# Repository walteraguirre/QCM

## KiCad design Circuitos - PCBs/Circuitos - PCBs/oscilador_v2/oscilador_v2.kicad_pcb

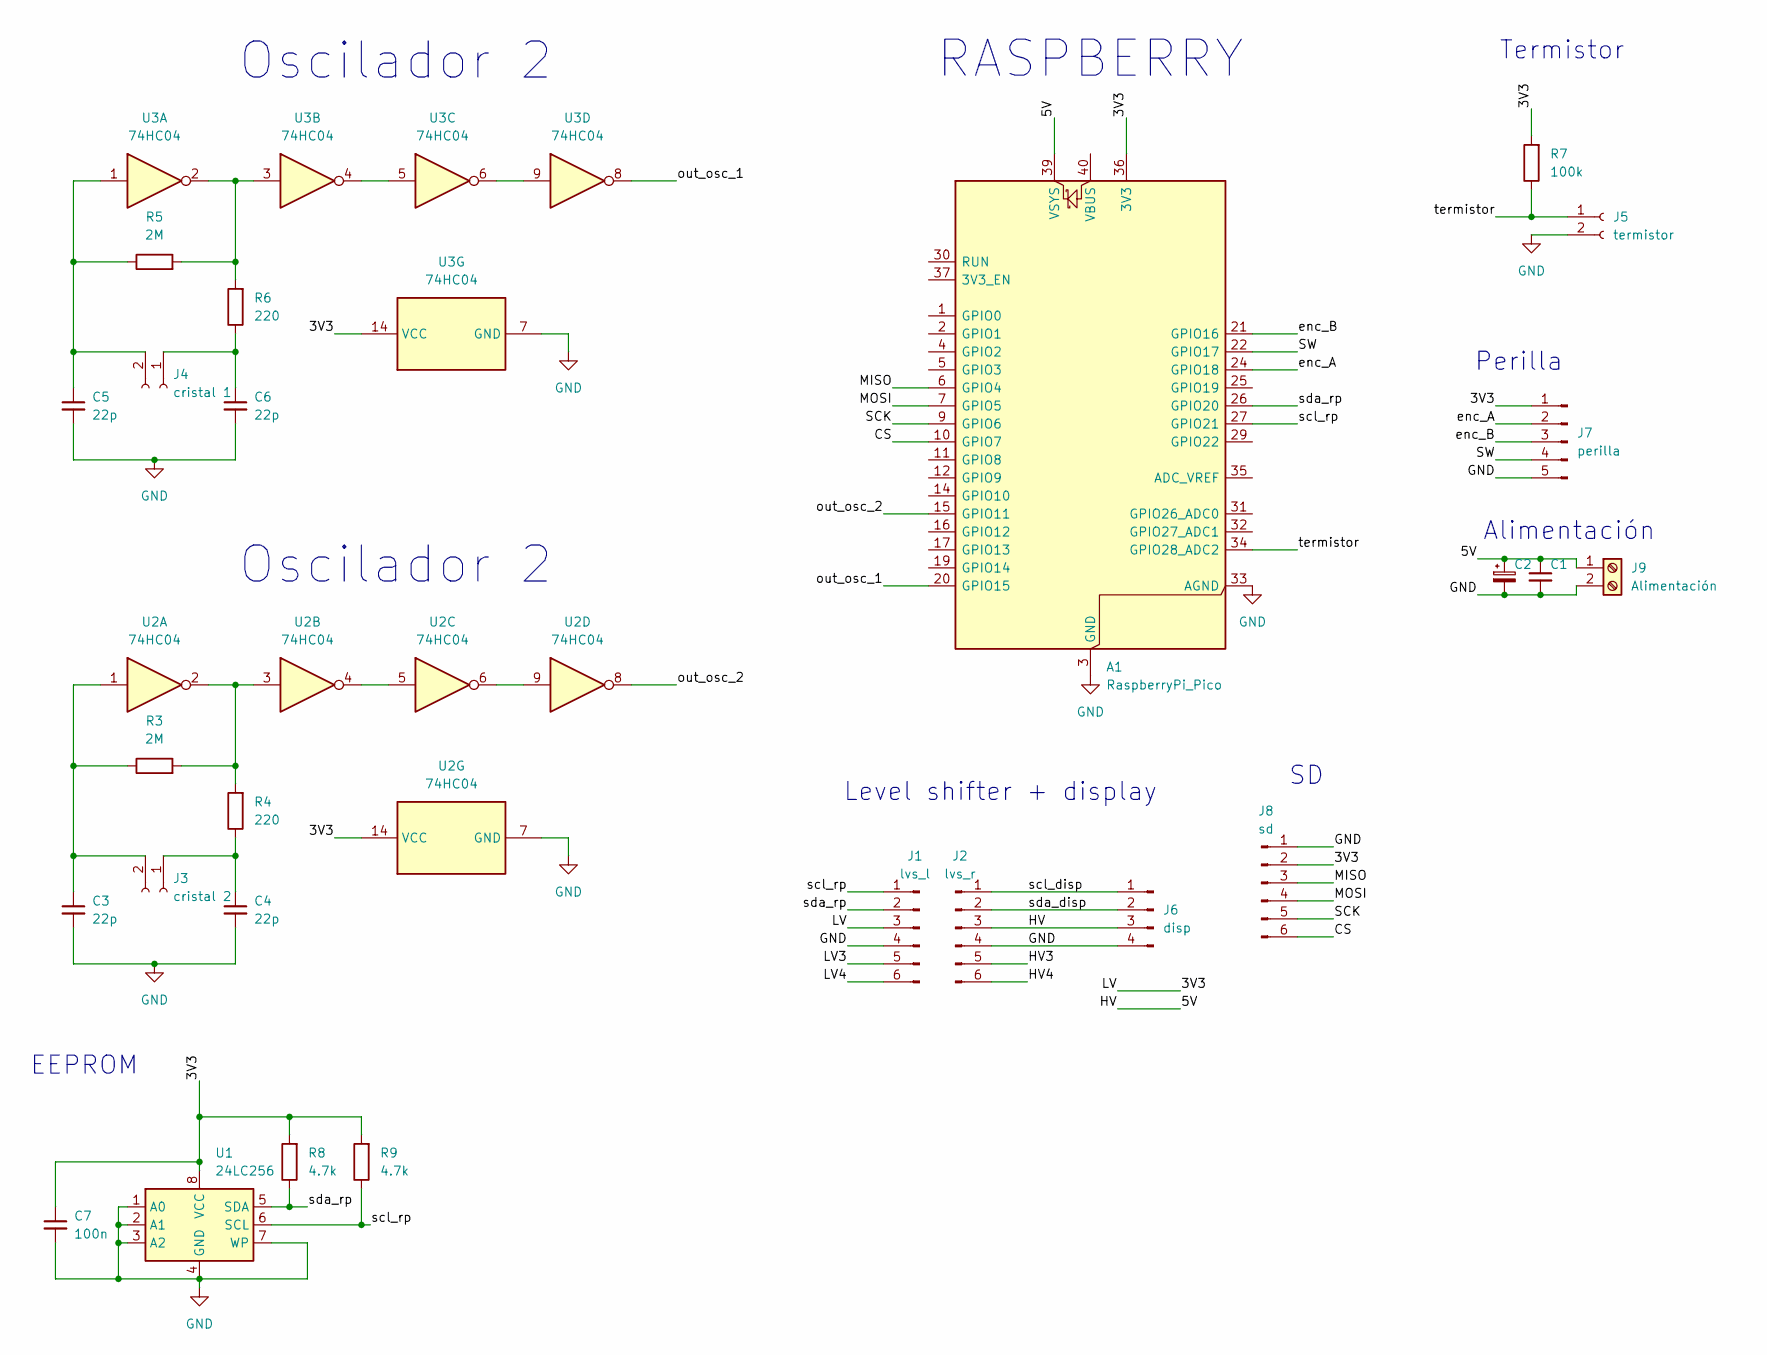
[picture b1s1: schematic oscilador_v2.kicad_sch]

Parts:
A1: RaspberryPi_Pico; RaspberryPi_Pico_Common_Unspecified
C1: C_Small; C_Disc_D10.0mm_W2.5mm_P5.00mm
C2: C_Polarized_Small; CP_Radial_D5.0mm_P2.50mm
C3, C4, C5, C6: 22p; C_Disc_D10.0mm_W2.5mm_P5.00mm
C7: 100n; C_Disc_D10.0mm_W2.5mm_P5.00mm
J1: lvs_l; PinSocket_1x06_P2.54mm_Vertical
J2: lvs_r; PinSocket_1x06_P2.54mm_Vertical
J3: cristal 2; JST_EH_B2B-EH-A_1x02_P2.50mm_Vertical
J4: cristal 1; JST_EH_B2B-EH-A_1x02_P2.50mm_Vertical
J5: termistor; JST_EH_B2B-EH-A_1x02_P2.50mm_Vertical
J6: disp; PinHeader_1x04_P2.54mm_Vertical
J7: perilla; PinHeader_1x05_P2.54mm_Vertical
J8: sd; PinSocket_1x06_P2.54mm_Vertical
J9: Alimentación; TerminalBlock_MaiXu_MX126-5.0-02P_1x02_P5.00mm
R3, R5: 2M; R_Axial_DIN0207_L6.3mm_D2.5mm_P10.16mm_Horizontal
R4, R6: 220; R_Axial_DIN0207_L6.3mm_D2.5mm_P10.16mm_Horizontal
R7: 100k; R_Axial_DIN0207_L6.3mm_D2.5mm_P10.16mm_Horizontal
R8, R9: 4.7k; R_Axial_DIN0207_L6.3mm_D2.5mm_P10.16mm_Horizontal
U1: 24LC256; DIP-8_W7.62mm_LongPads
U2, U3: 74HC04; DIP-14_W7.62mm

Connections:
/3V3: A1.36 (3V3), C7.1, J1.3, J7.1, J8.2, R7.2, R8.2, R9.2, U1.8 (VCC), U2.14 (VCC), U3.14 (VCC)
/5V: A1.39 (VSYS), C1.1, C2.1, J2.3, J6.3, J9.1
/CS: A1.10 (GPIO7), J8.6
/HV3: J2.5
/HV4: J2.6
/LV3: J1.5
/LV4: J1.6
/MISO: A1.6 (GPIO4), J8.3
/MOSI: A1.7 (GPIO5), J8.4
/SCK: A1.9 (GPIO6), J8.5
/SW: A1.22 (GPIO17), J7.4
/enc_A: A1.24 (GPIO18), J7.2
/enc_B: A1.21 (GPIO16), J7.3
/out_osc_1: A1.20 (GPIO15), U3.8
/out_osc_2: A1.15 (GPIO11), U2.8
/scl_disp: J2.1, J6.1
/scl_rp: A1.27 (GPIO21), J1.1, R9.1, U1.6 (SCL)
/sda_disp: J2.2, J6.2
/sda_rp: A1.26 (GPIO20), J1.2, R8.1, U1.5 (SDA)
/termistor: A1.34 (GPIO28_ADC2), J5.1, R7.1
GND: A1.3 (GND), A1.8 (GND), A1.13 (GND), A1.18 (GND), A1.23 (GND), A1.28 (GND), A1.33 (AGND), A1.38 (GND), C1.2, C2.2, C3.2, C4.2, C5.2, C6.2, C7.2, J1.4, J2.4, J5.2, J6.4, J7.5, J8.1, J9.2, U1.1 (A0), U1.2 (A1), U1.3 (A2), U1.4 (GND), U1.7 (WP), U2.7 (GND), U3.7 (GND)
unnamed: C4.1, J3.1, R4.1
unnamed: C3.1, J3.2, R3.1, U2.1
unnamed: C6.1, J4.1, R6.1
unnamed: C5.1, J4.2, R5.1, U3.1
unnamed: R3.2, R4.2, U2.2, U2.3
unnamed: R5.2, R6.2, U3.2, U3.3
unnamed: U2.4, U2.5
unnamed: U2.6, U2.9
unnamed: U3.4, U3.5
unnamed: U3.6, U3.9

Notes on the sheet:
Level shifter + display
Perilla
Alimentación
Oscilador 2
EEPROM
Termistor
RASPBERRY

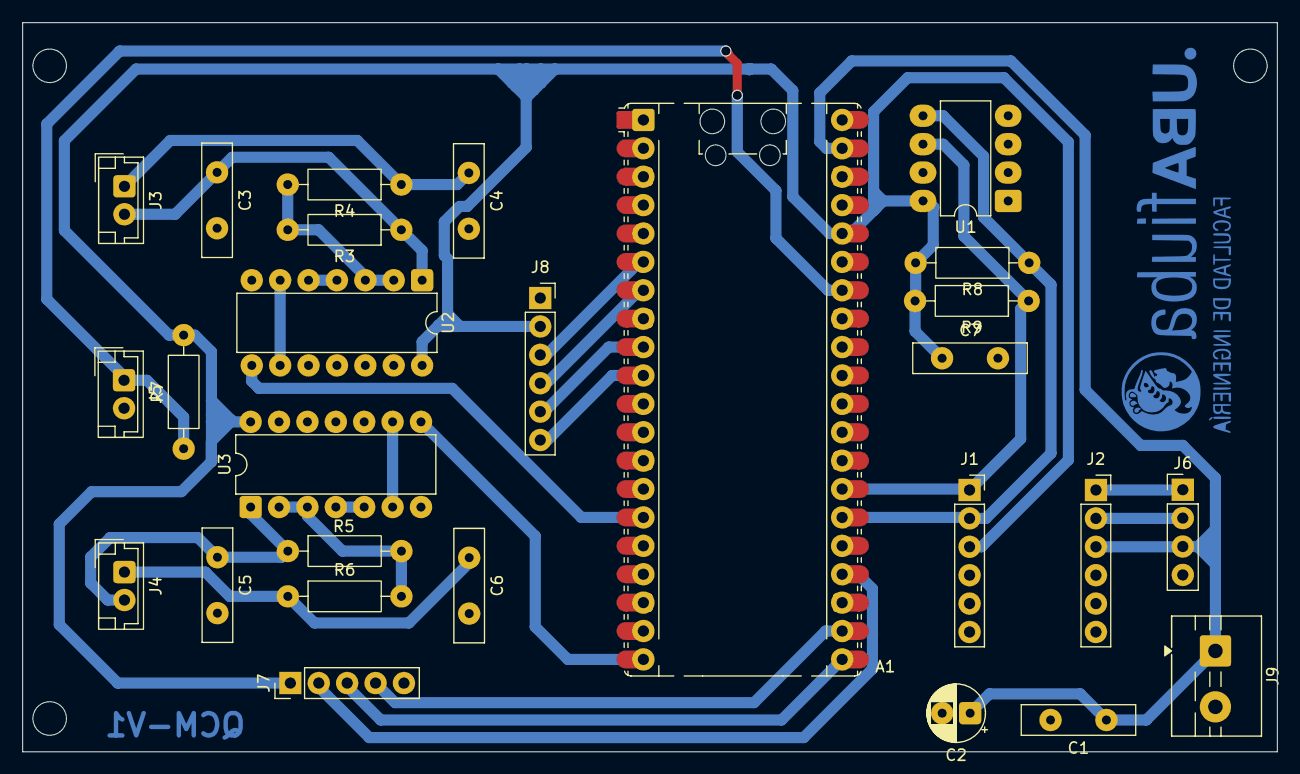
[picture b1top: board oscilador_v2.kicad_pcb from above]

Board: 2 copper layers, 112.2 x 65.2 mm, 27 parts (0 on the bottom side), 27 nets.

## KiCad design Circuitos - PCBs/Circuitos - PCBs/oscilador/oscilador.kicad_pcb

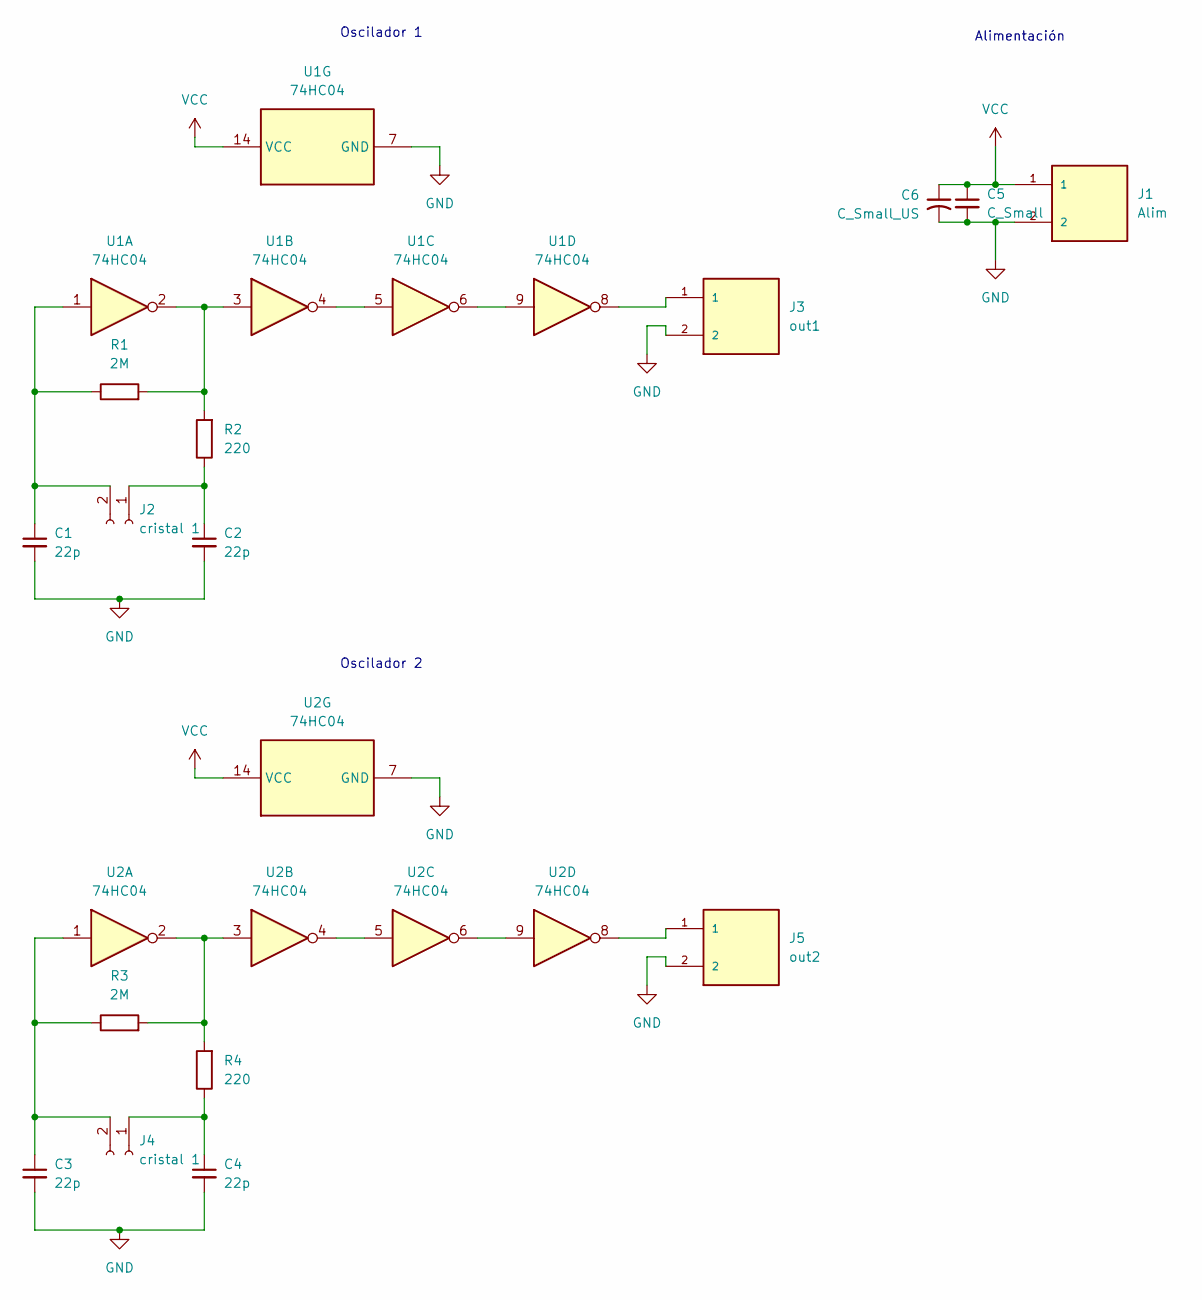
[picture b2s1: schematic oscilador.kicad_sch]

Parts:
C1, C2, C3, C4: 22p; C_Disc_D10.0mm_W2.5mm_P5.00mm
C5: C_Small; C_Disc_D10.0mm_W2.5mm_P5.00mm
C6: C_Small_US; CP_Radial_D6.3mm_P2.50mm
J1: Alim; HANDSON_KF301-2P; PARTREV NA
J2, J4: cristal 1; PinSocket_1x02_P2.54mm_Vertical
J3: out1; HANDSON_KF301-2P; PARTREV NA
J5: out2; HANDSON_KF301-2P; PARTREV NA
R1, R3: 2M; R_Axial_DIN0207_L6.3mm_D2.5mm_P10.16mm_Horizontal
R2, R4: 220; R_Axial_DIN0207_L6.3mm_D2.5mm_P10.16mm_Horizontal
U1, U2: 74HC04; DIP-14_W7.62mm

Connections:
GND: C1.2, C2.2, C3.2, C4.2, C5.2, C6.2, J1.2, J3.2, J5.2, U1.7 (GND), U2.7 (GND)
unnamed: C2.1, J2.1, R2.1
unnamed: C1.1, J2.2, R1.1, U1.1
unnamed: J3.1, U1.8
unnamed: C4.1, J4.1, R4.1
unnamed: C3.1, J4.2, R3.1, U2.1
unnamed: J5.1, U2.8
unnamed: R1.2, R2.2, U1.2, U1.3
unnamed: R3.2, R4.2, U2.2, U2.3
unnamed: U1.4, U1.5
unnamed: U1.6, U1.9
unnamed: U2.4, U2.5
unnamed: U2.6, U2.9
VCC: C5.1, C6.1, J1.1, U1.14 (VCC), U2.14 (VCC)

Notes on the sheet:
Oscilador 1
Oscilador 2
Alimentación

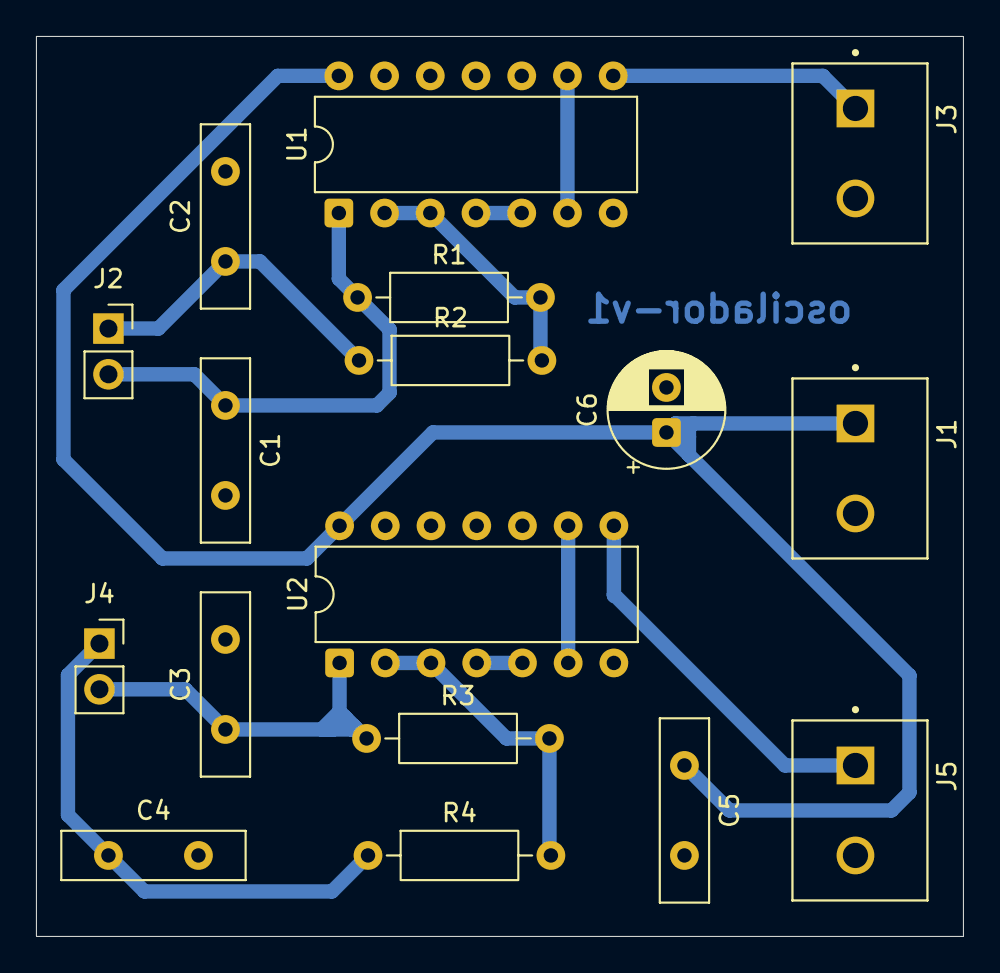
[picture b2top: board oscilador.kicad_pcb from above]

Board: 2 copper layers, 51.5 x 50.0 mm, 17 parts (0 on the bottom side), 14 nets.
